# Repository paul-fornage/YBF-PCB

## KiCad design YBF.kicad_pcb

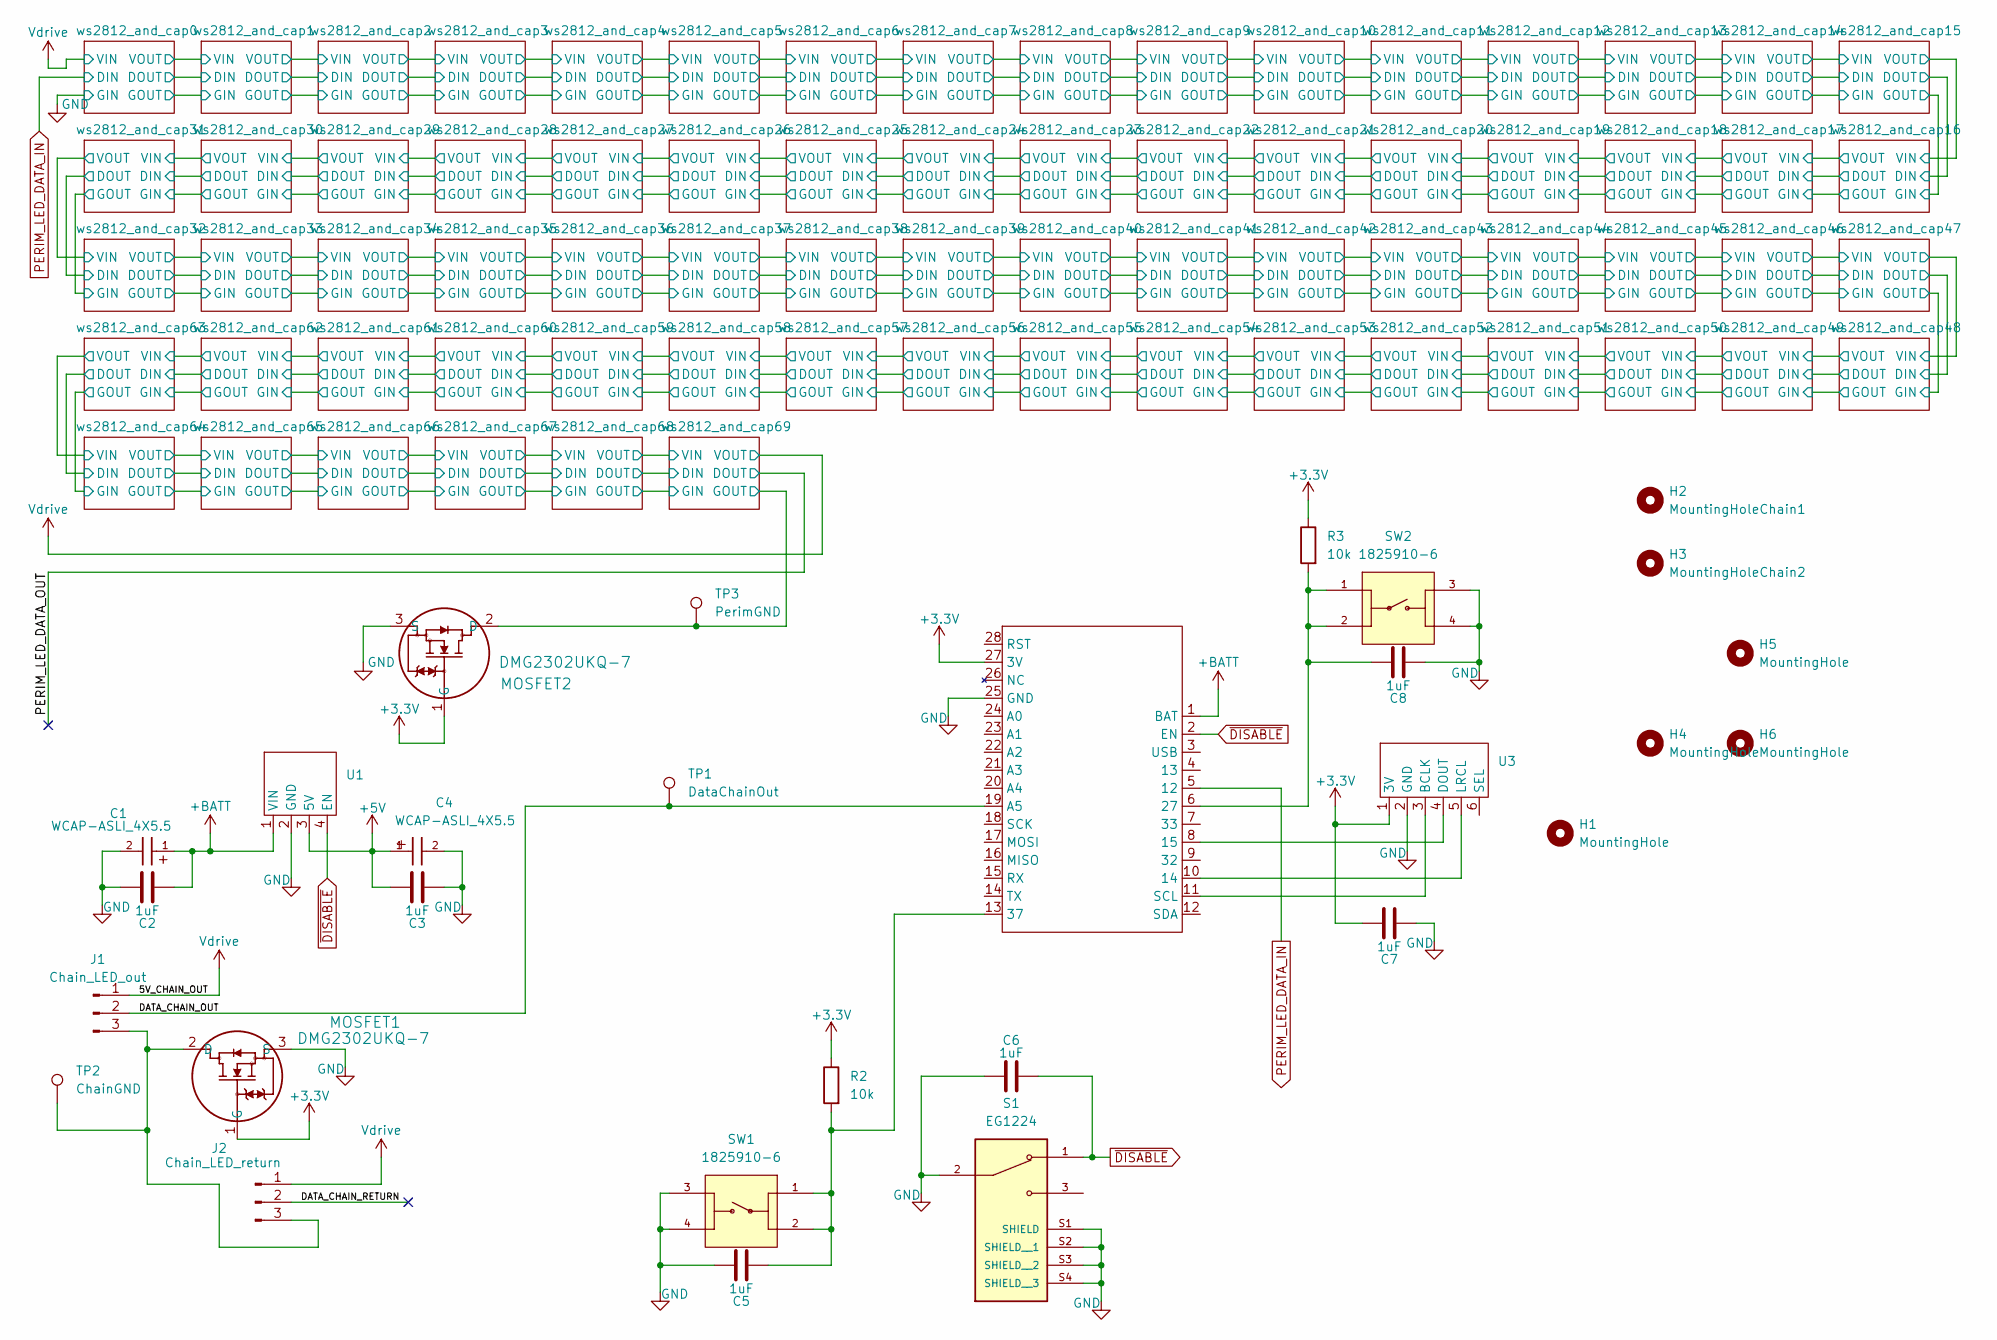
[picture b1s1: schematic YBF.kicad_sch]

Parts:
C1, C4: WCAP-ASLI_4X5.5; WCAP-ASLI_4X5.5_DXL_
C2, C3, C5, C6, C7, C8: 1uF; C_0603_1608Metric
H1: MountingHole; MountingHole_6mm
H2: MountingHoleChain1; MountingHole_2.1mm
H3: MountingHoleChain2; MountingHole_2.1mm
H4, H5, H6: MountingHole; MountingHole_3mm
J1: Chain_LED_out; JST_XH_B3B-XH-A_1x03_P2.50mm_Vertical
J2: Chain_LED_return; JST_XH_B3B-XH-A_1x03_P2.50mm_Vertical
MOSFET1, MOSFET2: DMG2302UKQ-7; SOT23_DMG2302_DIO
R2, R3: 10k; R_0603_1608Metric
S1: EG1224; SW_EG1224; PARTREV A
SW1, SW2: 1825910-6; SW_1825910-6-4; PARTREV C10
TP1: DataChainOut; PinHeader_1x01_P2.54mm_Vertical
TP2: ChainGND; PinHeader_1x01_P2.54mm_Vertical
TP3: PerimGND; PinHeader_1x01_P2.54mm_Vertical
U1: ADA4654_Mini_boost_5v
U2: ADA5400_ESP32_Feather
U3: ADA6049_ICS_43434_MICROPHONE

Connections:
+3.3V: C7.1, MOSFET1.1 (G), MOSFET2.1 (G), R2.1, R3.1, U2.27 (3V), U3.1 (3V); also elsewhere on the board
+5V: C3.1, C4.1, U1.3 (5V); also elsewhere on the board
+BATT: C1.1, C2.1, U1.1 (VIN), U2.1 (BAT); also elsewhere on the board
/DATA_CHAIN_OUT: J1.2, TP1.1, U2.19 (A5)
/DATA_CHAIN_RETURN: J2.2
GND: C1.2, C2.2, C3.2, C4.2, C5.2, C6.2, C7.2, C8.2, MOSFET1.3 (S), MOSFET2.3 (S), S1.2, S1.S1 (SHIELD), S1.S2 (SHIELD__1), S1.S3 (SHIELD__2), S1.S4 (SHIELD__3), SW1.3, SW1.4, SW2.3, SW2.4, U1.2 (GND), U2.25 (GND), U3.2 (GND); also elsewhere on the board
unnamed: U2.10 (14), U3.5 (LRCL)
unnamed: U2.8 (15), U3.4 (DOUT)
unnamed: C8.1, R3.2, SW2.1, SW2.2, U2.6 (27)
unnamed: C5.1, R2.2, SW1.1, SW1.2, U2.13 (37)
unnamed: U2.11 (SCL), U3.3 (BCLK)
PERIM_LED_DATA_IN: U2.5 (12); also elsewhere on the board
Vdrive: J1.1, J2.1; also elsewhere on the board
~DISABLE: C6.1, S1.1, U1.4 (EN), U2.2 (EN)

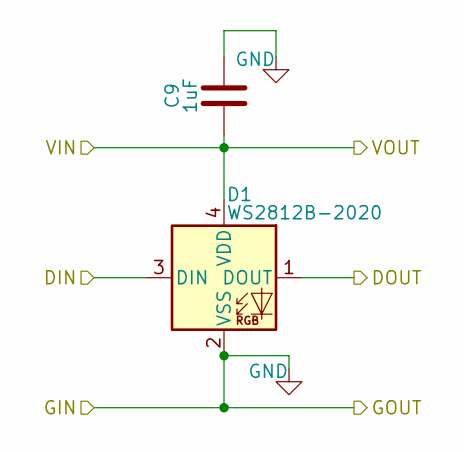
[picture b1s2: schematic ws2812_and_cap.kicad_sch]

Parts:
C9: 1uF; C_0603_1608Metric
D1: WS2812B-2020; LED_WS2812B-2020_PLCC4_2.0x2.0mm

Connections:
/ws2812_and_cap0/DOUT: D1.1 (DOUT); also elsewhere on the board
GND: C9.2, D1.2 (VSS); also elsewhere on the board
PERIM_LED_DATA_IN: D1.3 (DIN); also elsewhere on the board
Vdrive: C9.1, D1.4 (VDD); also elsewhere on the board

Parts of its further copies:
C10, C11, C12, C13, C14, C15, C16, C17, C18, C19, C20, C21, C22, C23, C24, C25, C26, C27, C28, C29, C30, C31, C32, C33, C34, C35, C36, C37, C38, C39, C40, C41, C42, C43, C44, C45, C46, C47, C48, C49, C50, C51, C52, C53, C54, C55, C56, C57, C58, C59, C60, C61, C62, C63, C64, C65, C66, C67, C68, C69, C70, C71, C72, C73, C74, C75, C76, C77, C78: 1uF; C_0603_1608Metric
D2, D3, D4, D5, D6, D7, D8, D9, D10, D11, D12, D13, D14, D15, D16, D17, D18, D19, D20, D21, D22, D23, D24, D25, D26, D27, D28, D29, D30, D31, D32, D33, D34, D35, D36, D37, D38, D39, D40, D41, D42, D43, D44, D45, D46, D47, D48, D49, D50, D51, D52, D53, D54, D55, D56, D57, D58, D59, D60, D61, D62, D63, D64, D65, D66, D67, D68, D69, D70: WS2812B-2020; LED_WS2812B-2020_PLCC4_2.0x2.0mm

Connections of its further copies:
/PERIM_LED_DATA_OUT: D70.1 (DOUT)
/ws2812_and_cap0/DOUT: D2.3 (DIN); also elsewhere on the board
/ws2812_and_cap1/DOUT: D2.1 (DOUT), D3.3 (DIN)
/ws2812_and_cap2/DOUT: D3.1 (DOUT), D4.3 (DIN)
/ws2812_and_cap3/DOUT: D4.1 (DOUT), D5.3 (DIN)
/ws2812_and_cap4/DOUT: D5.1 (DOUT), D6.3 (DIN)
/ws2812_and_cap5/DOUT: D6.1 (DOUT), D7.3 (DIN)
/ws2812_and_cap6/DOUT: D7.1 (DOUT), D8.3 (DIN)
/ws2812_and_cap7/DOUT: D8.1 (DOUT), D9.3 (DIN)
/ws2812_and_cap8/DOUT: D9.1 (DOUT), D10.3 (DIN)
/ws2812_and_cap10/DIN: D10.1 (DOUT), D11.3 (DIN)
/ws2812_and_cap10/DOUT: D11.1 (DOUT), D12.3 (DIN)
/ws2812_and_cap11/DOUT: D12.1 (DOUT), D13.3 (DIN)
/ws2812_and_cap12/DOUT: D13.1 (DOUT), D14.3 (DIN)
/ws2812_and_cap13/DOUT: D14.1 (DOUT), D15.3 (DIN)
/ws2812_and_cap14/DOUT: D15.1 (DOUT), D16.3 (DIN)
/ws2812_and_cap15/DOUT: D16.1 (DOUT), D17.3 (DIN)
/ws2812_and_cap16/DOUT: D17.1 (DOUT), D18.3 (DIN)
/ws2812_and_cap17/DOUT: D18.1 (DOUT), D19.3 (DIN)
/ws2812_and_cap18/DOUT: D19.1 (DOUT), D20.3 (DIN)
/ws2812_and_cap19/DOUT: D20.1 (DOUT), D21.3 (DIN)
/ws2812_and_cap20/DOUT: D21.1 (DOUT), D22.3 (DIN)
/ws2812_and_cap21/DOUT: D22.1 (DOUT), D23.3 (DIN)
/ws2812_and_cap22/DOUT: D23.1 (DOUT), D24.3 (DIN)
/ws2812_and_cap23/DOUT: D24.1 (DOUT), D25.3 (DIN)
/ws2812_and_cap24/DOUT: D25.1 (DOUT), D26.3 (DIN)
/ws2812_and_cap25/DOUT: D26.1 (DOUT), D27.3 (DIN)
/ws2812_and_cap26/DOUT: D27.1 (DOUT), D28.3 (DIN)
/ws2812_and_cap27/DOUT: D28.1 (DOUT), D29.3 (DIN)
/ws2812_and_cap28/DOUT: D29.1 (DOUT), D30.3 (DIN)
/ws2812_and_cap29/DOUT: D30.1 (DOUT), D31.3 (DIN)
/ws2812_and_cap30/DOUT: D31.1 (DOUT), D32.3 (DIN)
/ws2812_and_cap31/DOUT: D32.1 (DOUT), D33.3 (DIN)
/ws2812_and_cap32/DOUT: D33.1 (DOUT), D34.3 (DIN)
/ws2812_and_cap33/DOUT: D34.1 (DOUT), D35.3 (DIN)
/ws2812_and_cap34/DOUT: D35.1 (DOUT), D36.3 (DIN)
/ws2812_and_cap35/DOUT: D36.1 (DOUT), D37.3 (DIN)
/ws2812_and_cap36/DOUT: D37.1 (DOUT), D38.3 (DIN)
/ws2812_and_cap37/DOUT: D38.1 (DOUT), D39.3 (DIN)
/ws2812_and_cap38/DOUT: D39.1 (DOUT), D40.3 (DIN)
/ws2812_and_cap39/DOUT: D40.1 (DOUT), D41.3 (DIN)
/ws2812_and_cap40/DOUT: D41.1 (DOUT), D42.3 (DIN)
/ws2812_and_cap41/DOUT: D42.1 (DOUT), D43.3 (DIN)
/ws2812_and_cap42/DOUT: D43.1 (DOUT), D44.3 (DIN)
/ws2812_and_cap43/DOUT: D44.1 (DOUT), D45.3 (DIN)
/ws2812_and_cap44/DOUT: D45.1 (DOUT), D46.3 (DIN)
/ws2812_and_cap45/DOUT: D46.1 (DOUT), D47.3 (DIN)
/ws2812_and_cap46/DOUT: D47.1 (DOUT), D48.3 (DIN)
/ws2812_and_cap47/DOUT: D48.1 (DOUT), D49.3 (DIN)
/ws2812_and_cap48/DOUT: D49.1 (DOUT), D50.3 (DIN)
/ws2812_and_cap49/DOUT: D50.1 (DOUT), D51.3 (DIN)
/ws2812_and_cap50/DOUT: D51.1 (DOUT), D52.3 (DIN)
/ws2812_and_cap51/DOUT: D52.1 (DOUT), D53.3 (DIN)
/ws2812_and_cap52/DOUT: D53.1 (DOUT), D54.3 (DIN)
/ws2812_and_cap53/DOUT: D54.1 (DOUT), D55.3 (DIN)
/ws2812_and_cap54/DOUT: D55.1 (DOUT), D56.3 (DIN)
/ws2812_and_cap55/DOUT: D56.1 (DOUT), D57.3 (DIN)
/ws2812_and_cap56/DOUT: D57.1 (DOUT), D58.3 (DIN)
/ws2812_and_cap57/DOUT: D58.1 (DOUT), D59.3 (DIN)
/ws2812_and_cap58/DOUT: D59.1 (DOUT), D60.3 (DIN)
/ws2812_and_cap59/DOUT: D60.1 (DOUT), D61.3 (DIN)
/ws2812_and_cap60/DOUT: D61.1 (DOUT), D62.3 (DIN)
/ws2812_and_cap61/DOUT: D62.1 (DOUT), D63.3 (DIN)
/ws2812_and_cap62/DOUT: D63.1 (DOUT), D64.3 (DIN)
/ws2812_and_cap63/DOUT: D64.1 (DOUT), D65.3 (DIN)
/ws2812_and_cap64/DOUT: D65.1 (DOUT), D66.3 (DIN)
/ws2812_and_cap65/DOUT: D66.1 (DOUT), D67.3 (DIN)
/ws2812_and_cap66/DOUT: D67.1 (DOUT), D68.3 (DIN)
/ws2812_and_cap67/DOUT: D68.1 (DOUT), D69.3 (DIN)
/ws2812_and_cap68/DOUT: D69.1 (DOUT), D70.3 (DIN)
GND: C10.2, C11.2, C12.2, C13.2, C14.2, C15.2, C16.2, C17.2, C18.2, C19.2, C20.2, C21.2, C22.2, C23.2, C24.2, C25.2, C26.2, C27.2, C28.2, C29.2, C30.2, C31.2, C32.2, C33.2, C34.2, C35.2, C36.2, C37.2, C38.2, C39.2, C40.2, C41.2, C42.2, C43.2, C44.2, C45.2, C46.2, C47.2, C48.2, C49.2, C50.2, C51.2, C52.2, C53.2, C54.2, C55.2, C56.2, C57.2, C58.2, C59.2, C60.2, C61.2, C62.2, C63.2, C64.2, C65.2, C66.2, C67.2, C68.2, C69.2, C70.2, C71.2, C72.2, C73.2, C74.2, C75.2, C76.2, C77.2, C78.2, D2.2 (VSS), D3.2 (VSS), D4.2 (VSS), D5.2 (VSS), D6.2 (VSS), D7.2 (VSS), D8.2 (VSS), D9.2 (VSS), D10.2 (VSS), D11.2 (VSS), D12.2 (VSS), D13.2 (VSS), D14.2 (VSS), D15.2 (VSS), D16.2 (VSS), D17.2 (VSS), D18.2 (VSS), D19.2 (VSS), D20.2 (VSS), D21.2 (VSS), D22.2 (VSS), D23.2 (VSS), D24.2 (VSS), D25.2 (VSS), D26.2 (VSS), D27.2 (VSS), D28.2 (VSS), D29.2 (VSS), D30.2 (VSS), D31.2 (VSS), D32.2 (VSS), D33.2 (VSS), D34.2 (VSS), D35.2 (VSS), D36.2 (VSS), D37.2 (VSS), D38.2 (VSS), D39.2 (VSS), D40.2 (VSS), D41.2 (VSS), D42.2 (VSS), D43.2 (VSS), D44.2 (VSS), D45.2 (VSS), D46.2 (VSS), D47.2 (VSS), D48.2 (VSS), D49.2 (VSS), D50.2 (VSS), D51.2 (VSS), D52.2 (VSS), D53.2 (VSS), D54.2 (VSS), D55.2 (VSS), D56.2 (VSS), D57.2 (VSS), D58.2 (VSS), D59.2 (VSS), D60.2 (VSS), D61.2 (VSS), D62.2 (VSS), D63.2 (VSS), D64.2 (VSS), D65.2 (VSS), D66.2 (VSS), D67.2 (VSS), D68.2 (VSS), D69.2 (VSS), D70.2 (VSS); also elsewhere on the board
Vdrive: C10.1, C11.1, C12.1, C13.1, C14.1, C15.1, C16.1, C17.1, C18.1, C19.1, C20.1, C21.1, C22.1, C23.1, C24.1, C25.1, C26.1, C27.1, C28.1, C29.1, C30.1, C31.1, C32.1, C33.1, C34.1, C35.1, C36.1, C37.1, C38.1, C39.1, C40.1, C41.1, C42.1, C43.1, C44.1, C45.1, C46.1, C47.1, C48.1, C49.1, C50.1, C51.1, C52.1, C53.1, C54.1, C55.1, C56.1, C57.1, C58.1, C59.1, C60.1, C61.1, C62.1, C63.1, C64.1, C65.1, C66.1, C67.1, C68.1, C69.1, C70.1, C71.1, C72.1, C73.1, C74.1, C75.1, C76.1, C77.1, C78.1, D2.4 (VDD), D3.4 (VDD), D4.4 (VDD), D5.4 (VDD), D6.4 (VDD), D7.4 (VDD), D8.4 (VDD), D9.4 (VDD), D10.4 (VDD), D11.4 (VDD), D12.4 (VDD), D13.4 (VDD), D14.4 (VDD), D15.4 (VDD), D16.4 (VDD), D17.4 (VDD), D18.4 (VDD), D19.4 (VDD), D20.4 (VDD), D21.4 (VDD), D22.4 (VDD), D23.4 (VDD), D24.4 (VDD), D25.4 (VDD), D26.4 (VDD), D27.4 (VDD), D28.4 (VDD), D29.4 (VDD), D30.4 (VDD), D31.4 (VDD), D32.4 (VDD), D33.4 (VDD), D34.4 (VDD), D35.4 (VDD), D36.4 (VDD), D37.4 (VDD), D38.4 (VDD), D39.4 (VDD), D40.4 (VDD), D41.4 (VDD), D42.4 (VDD), D43.4 (VDD), D44.4 (VDD), D45.4 (VDD), D46.4 (VDD), D47.4 (VDD), D48.4 (VDD), D49.4 (VDD), D50.4 (VDD), D51.4 (VDD), D52.4 (VDD), D53.4 (VDD), D54.4 (VDD), D55.4 (VDD), D56.4 (VDD), D57.4 (VDD), D58.4 (VDD), D59.4 (VDD), D60.4 (VDD), D61.4 (VDD), D62.4 (VDD), D63.4 (VDD), D64.4 (VDD), D65.4 (VDD), D66.4 (VDD), D67.4 (VDD), D68.4 (VDD), D69.4 (VDD), D70.4 (VDD); also elsewhere on the board

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
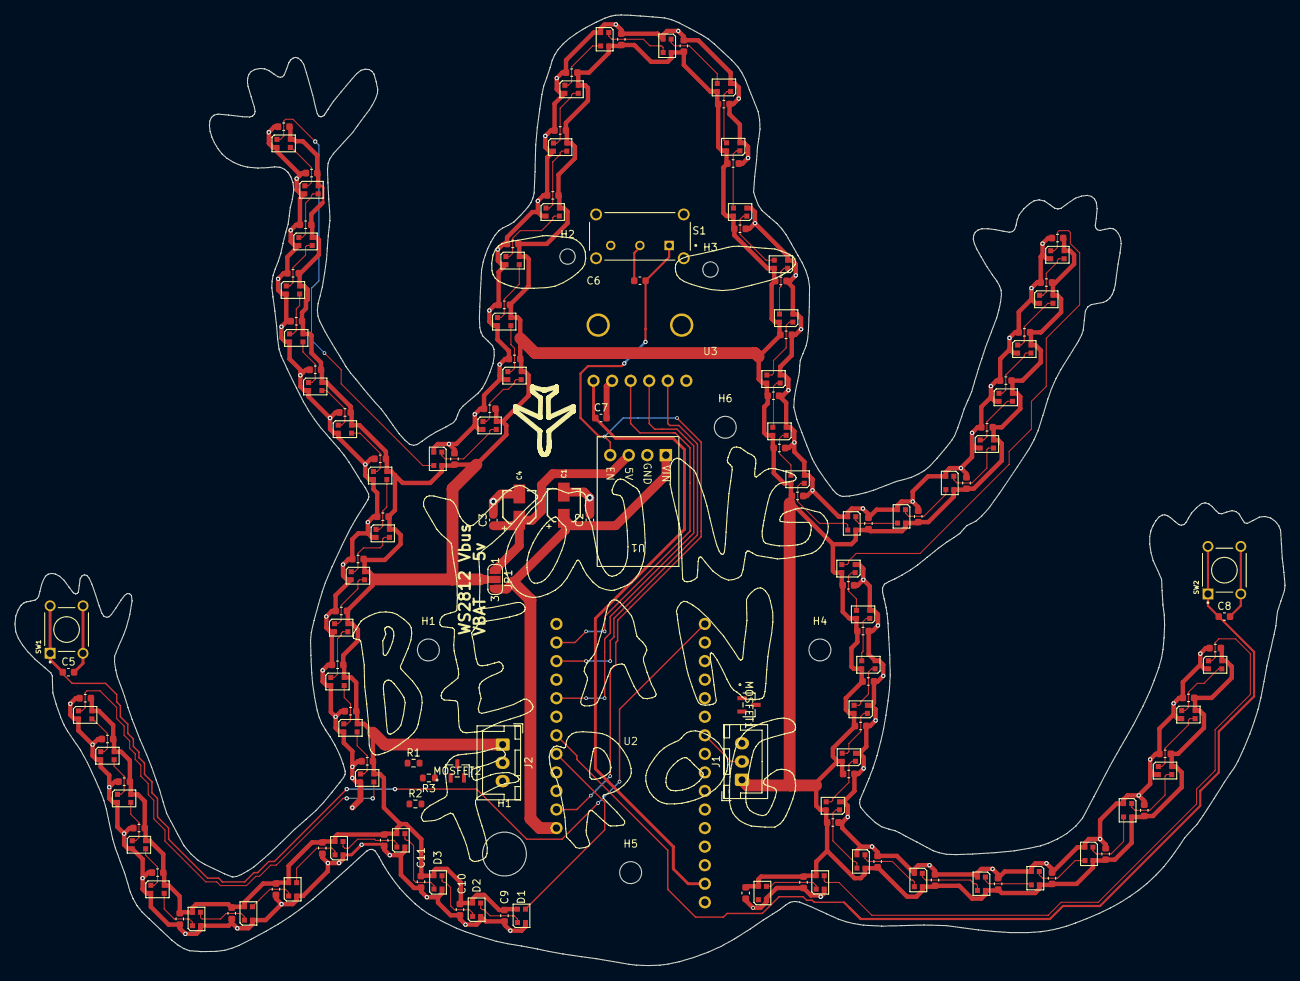
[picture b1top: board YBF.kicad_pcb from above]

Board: 2 copper layers, 173.9 x 130.1 mm, 169 parts (0 on the bottom side), 84 nets.

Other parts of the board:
H1#2: MountingHole; MountingHole_6mm
JP1: SolderJumper_3_Open; SolderJumper-3_P1.3mm_Open_RoundedPad1.0x1.5mm_NumberLabels
R1: 1M; R_0603_1608Metric

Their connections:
+3.3V: R1.2; also elsewhere on the board
+5V: JP1.1 (A); also elsewhere on the board
+BATT: JP1.3 (B); also elsewhere on the board
GND: R1.1; also elsewhere on the board
Vdrive: JP1.2 (C); also elsewhere on the board

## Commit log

2025-09-16 init
2025-09-27 progress
2025-09-27 Hieracrchical PCB
2025-09-27 place perim LEDs
2025-09-27 routing progress
2025-09-27 finish LED routing
2025-09-28 more routing
2025-09-28 v0.0.1
2025-09-28 v0.0.2
    add mounting holes and seperate chain and perim led lines
2025-09-29 Add chain loop holes
2025-10-13 add preliminary power saving FETS
2025-10-13 supporting FET impl
2025-10-14 add fet
2025-10-23 started on FETs
